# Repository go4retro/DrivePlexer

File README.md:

# DrivePlexer - A Floppy Drive Multiplexer system
The PCB converts the DRIVE1,2,3 lines of the standard floppy controller from discrete signals to a binary floppy drive "address"

## Assumptions
* MOTOR_ON can be used to enable the drives, so all 8 selects can be used.  If this is not true, the MOTOR_EN signal going to the decoder can be strapped to ground, which means DRIVE8 must be not connected (all high lines will be treated as no drive selected)

## License
Copyright (C) 2018  RETRO Innovations

These files are free designs; you can redistribute them and/or modify
them under the terms of the Creative Commons Attribution-ShareAlike 
4.0 International License.

You should have received a copy of the license along with this
work. If not, see <http://creativecommons.org/licenses/by-sa/4.0/>.

These files are distributed in the hope that they will be useful,
but WITHOUT ANY WARRANTY; without even the implied warranty of
MERCHANTABILITY or FITNESS FOR A PARTICULAR PURPOSE.  See the
license for more details.

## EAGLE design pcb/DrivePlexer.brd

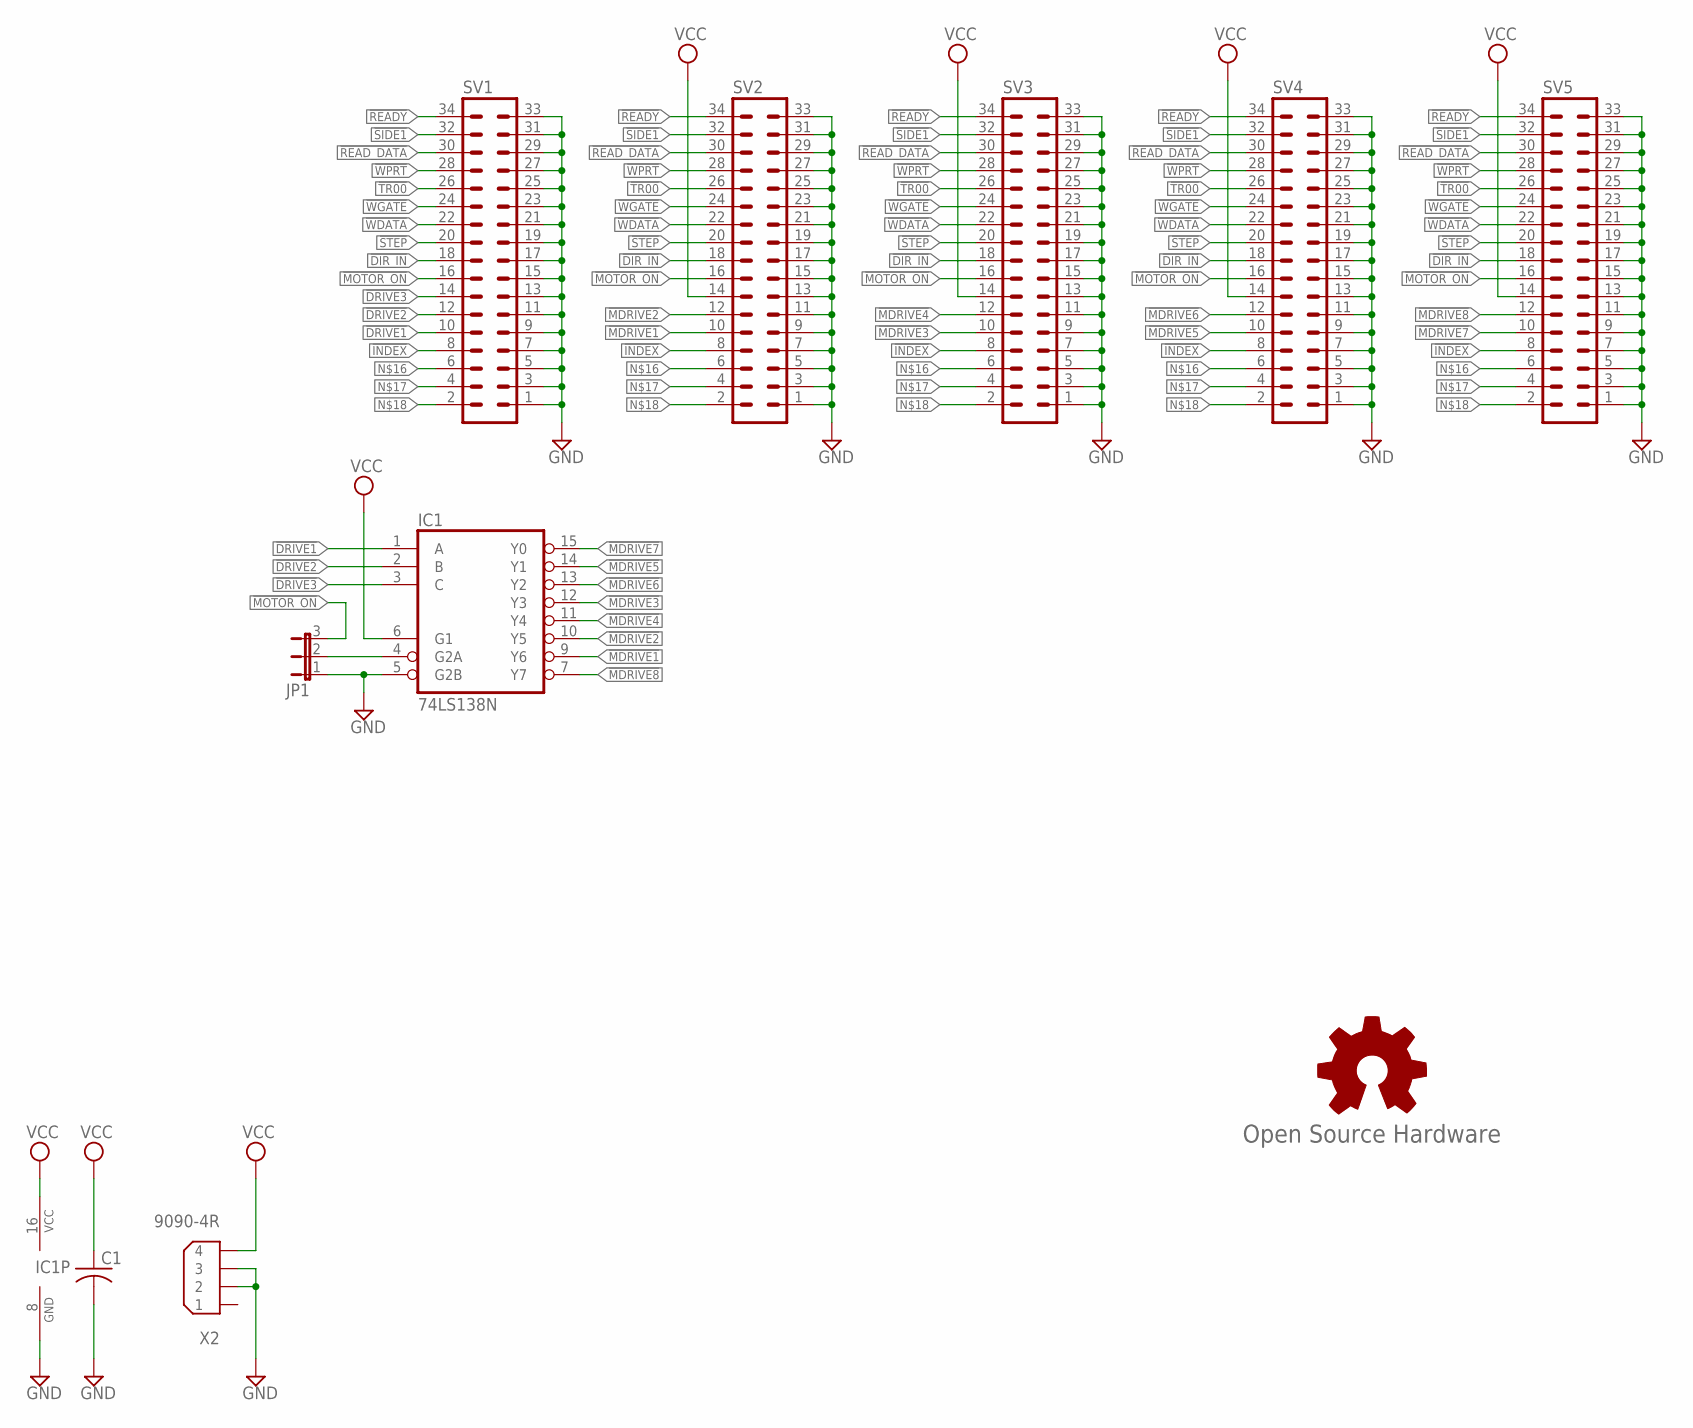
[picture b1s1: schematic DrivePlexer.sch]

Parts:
C1: C-US025-025X050; C025-025X050
GOLD_ORB_SM1: Open Source Hardware; OSHW_5MM
IC1: 74LS138N; DIL16-RP
JP1: JP2E; JP2
SV1, SV2, SV3, SV4, SV5: MA17-2
X2: 9090-4R

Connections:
!DIR_IN: SV1.18, SV2.18, SV3.18, SV4.18, SV5.18
!DRIVE1: IC1.1 (A), SV1.10
!DRIVE2: IC1.2 (B), SV1.12
!DRIVE3: IC1.3 (C), SV1.14
!INDEX: SV1.8, SV2.8, SV3.8, SV4.8, SV5.8
!MDRIVE1: IC1.9 (Y6), SV2.10
!MDRIVE2: IC1.10 (Y5), SV2.12
!MDRIVE3: IC1.12 (Y3), SV3.10
!MDRIVE4: IC1.11 (Y4), SV3.12
!MDRIVE5: IC1.14 (Y1), SV4.10
!MDRIVE6: IC1.13 (Y2), SV4.12
!MDRIVE7: IC1.15 (Y0), SV5.10
!MDRIVE8: IC1.7 (Y7), SV5.12
!MOTOR_ON: JP1.3, SV1.16, SV2.16, SV3.16, SV4.16, SV5.16
!READY: SV1.34, SV2.34, SV3.34, SV4.34, SV5.34
!READ_DATA: SV1.30, SV2.30, SV3.30, SV4.30, SV5.30
!SIDE1: SV1.32, SV2.32, SV3.32, SV4.32, SV5.32
!STEP: SV1.20, SV2.20, SV3.20, SV4.20, SV5.20
!TR00: SV1.26, SV2.26, SV3.26, SV4.26, SV5.26
!WDATA: SV1.22, SV2.22, SV3.22, SV4.22, SV5.22
!WGATE: SV1.24, SV2.24, SV3.24, SV4.24, SV5.24
!WPRT: SV1.28, SV2.28, SV3.28, SV4.28, SV5.28
GND: C1.2, IC1.5 (G2B), IC1.8 (GND), JP1.1, SV1.1, SV1.3, SV1.5, SV1.7, SV1.9, SV1.11, SV1.13, SV1.15, SV1.17, SV1.19, SV1.21, SV1.23, SV1.25, SV1.27, SV1.29, SV1.31, SV1.33, SV2.1, SV2.3, SV2.5, SV2.7, SV2.9, SV2.11, SV2.13, SV2.15, SV2.17, SV2.19, SV2.21, SV2.23, SV2.25, SV2.27, SV2.29, SV2.31, SV2.33, SV3.1, SV3.3, SV3.5, SV3.7, SV3.9, SV3.11, SV3.13, SV3.15, SV3.17, SV3.19, SV3.21, SV3.23, SV3.25, SV3.27, SV3.29, SV3.31, SV3.33, SV4.1, SV4.3, SV4.5, SV4.7, SV4.9, SV4.11, SV4.13, SV4.15, SV4.17, SV4.19, SV4.21, SV4.23, SV4.25, SV4.27, SV4.29, SV4.31, SV4.33, SV5.1, SV5.3, SV5.5, SV5.7, SV5.9, SV5.11, SV5.13, SV5.15, SV5.17, SV5.19, SV5.21, SV5.23, SV5.25, SV5.27, SV5.29, SV5.31, SV5.33, X2.2, X2.3
unnamed: IC1.4 (G2A), JP1.2
unnamed: SV1.6, SV2.6, SV3.6, SV4.6, SV5.6
unnamed: SV1.4, SV2.4, SV3.4, SV4.4, SV5.4
unnamed: SV1.2, SV2.2, SV3.2, SV4.2, SV5.2
VCC: C1.1, IC1.6 (G1), IC1.16 (VCC), SV2.14, SV3.14, SV4.14, SV5.14, X2.4

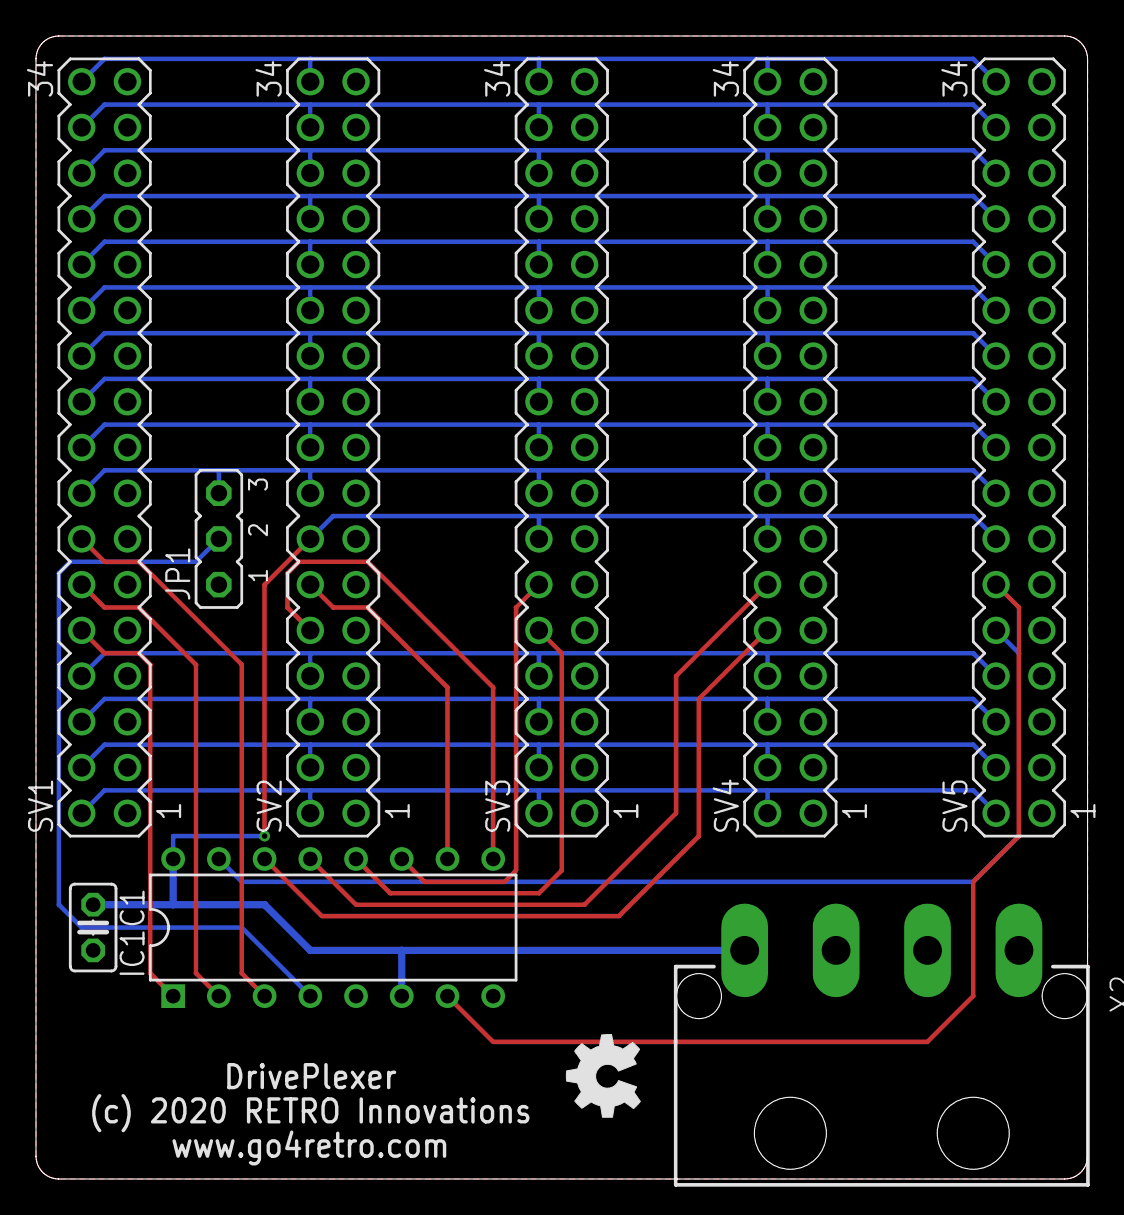
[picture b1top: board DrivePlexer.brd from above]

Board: 2 copper layers, 58.4 x 63.5 mm, 10 parts (0 on the bottom side), 28 nets.

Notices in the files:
pcb/DrivePlexer.brd:
(c) 2020 RETRO Innovations
